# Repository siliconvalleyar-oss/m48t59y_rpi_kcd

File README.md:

# m48t59y_rpi_kcd

Diseño de PCB en KiCad para interfaz M48T59Y (RTC/NVRAM) con PIC18F.

## Estructura

- `m48t59y_pic18f.kicad_pro` - Proyecto principal
- `m48t59y_pic18f.kicad_sch` - Esquemático principal
- `m48t59y_pic18f.kicad_pcb` - Layout PCB

## Módulos

- `power.kicad_sch` - Alimentación
- `mcu.kicad_sch` - Microcontrolador PIC18F
- `m48t59y.kicad_sch` - Circuito M48T59Y
- `txs0108e.kicad_sch` - Traductor de niveles TXS0108E
- `oled.kicad_sch` - Display OLED
- `led_sw.kicad_sch` - LEDs y switches
- `uart.kicad_sch` - UART
- `xt.kicad_sch` - Cristal

## Documentación

Imágenes de referencia en la carpeta `docs/`.

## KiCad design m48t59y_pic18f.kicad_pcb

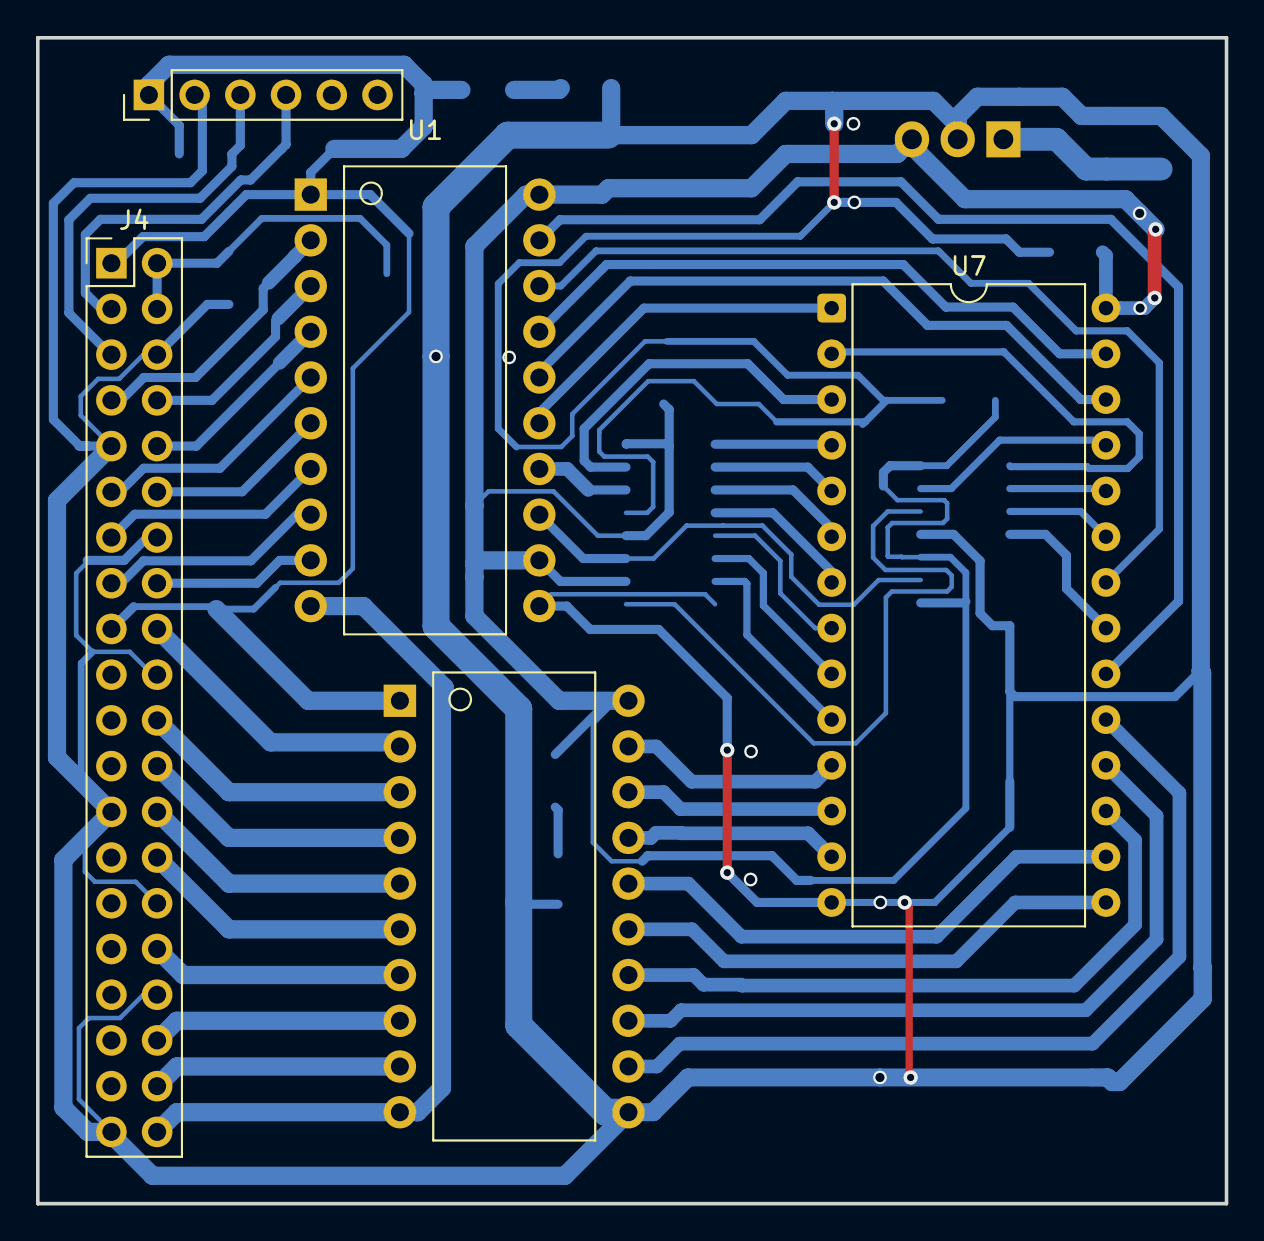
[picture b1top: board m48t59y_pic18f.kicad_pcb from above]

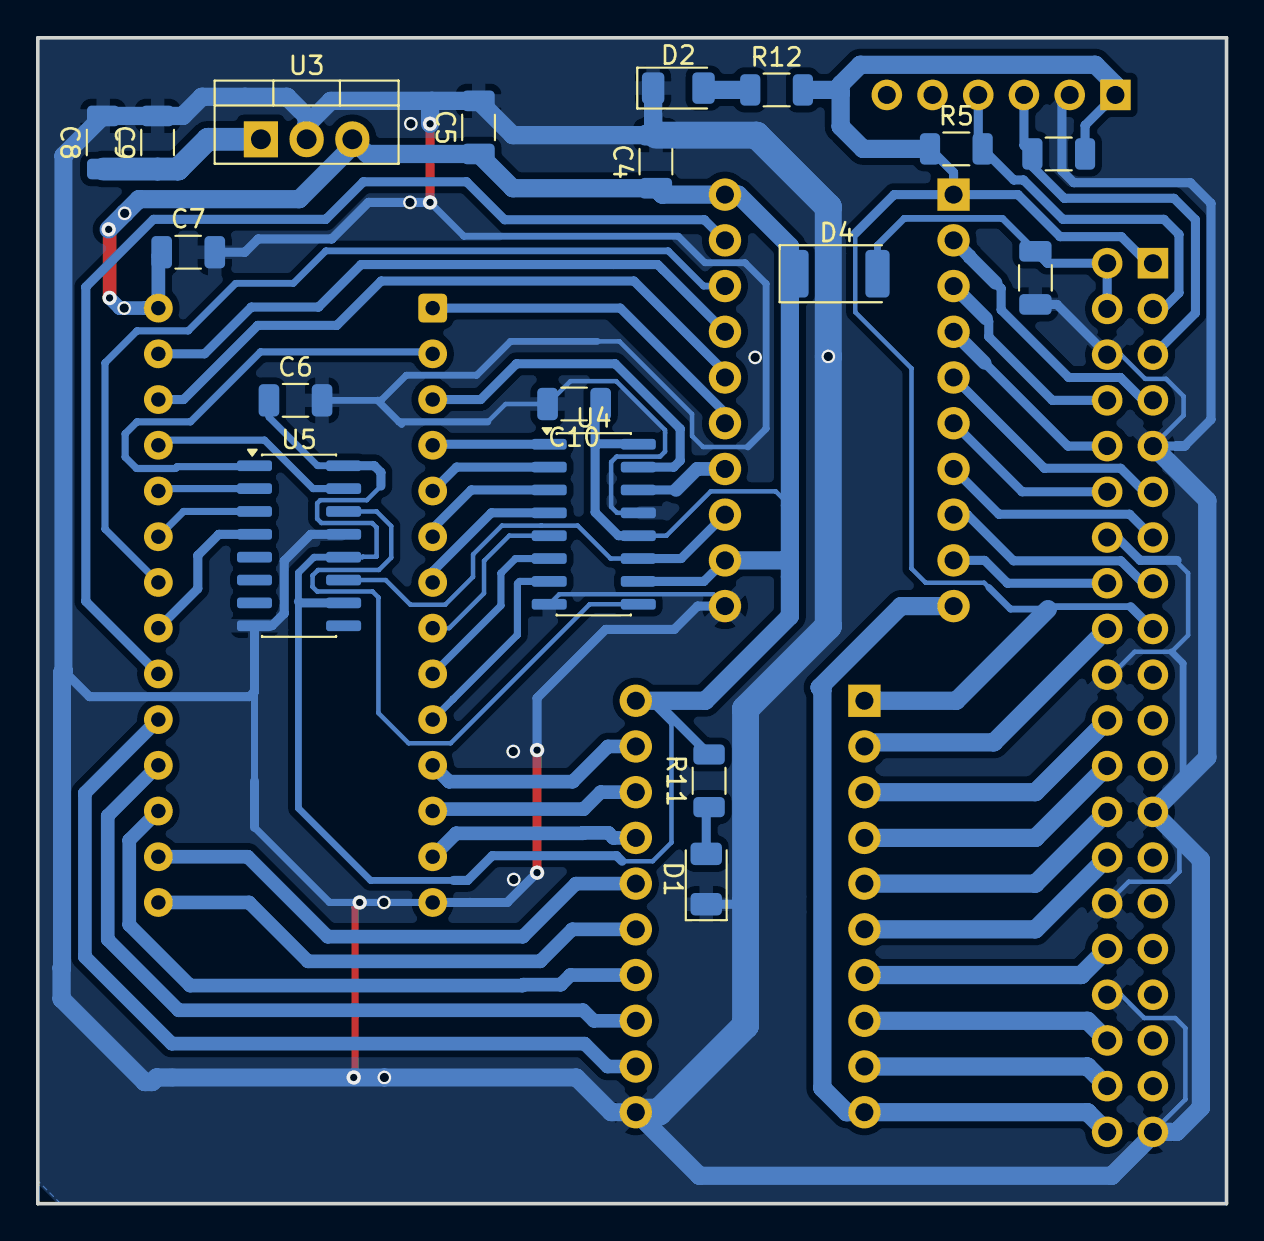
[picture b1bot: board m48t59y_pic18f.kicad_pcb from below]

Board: 2 copper layers, 66.0 x 64.8 mm, 23 parts (18 on the bottom side), 55 nets.

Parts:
C3, C4, C5, C6, C7, C8, C9, C10: 100n; C_1206_3216Metric
D1, D2: LED; LED_1206_3216Metric
D4: 1N4001; D_2010_5025Metric
J3: ssd1306; PinHeader_1x06_P2.54mm_Vertical
J4: Raspberry_Pi_4; PinHeader_2x20_P2.54mm_Vertical
R5, R6, R11, R12: 2k2; R_1206_3216Metric
U1, U2: TXS0108; TXS0108E_THT_20pin
U3: LM7805_TO220; TO-220-3_Vertical
U4, U5: 74HC595; SOIC-16_3.9x9.9mm_P1.27mm
U7: M48T08-150PC; DIP-28_W15.24mm

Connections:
+3V3: J3.1, J4.1 (3V3), J4.17 (3V3), R5.1, R6.1, R12.2, U1.1 (VCCA), U2.1 (VCCA)
+5V: C4.1, C5.1, C6.1, C7.1, C10.1, D4.1 (K), R11.2, U1.12 (B8), U1.20 (VCCB), U2.20 (VCCB), U3.3 (VO), U4.10 (~SRCLR), U4.12 (RCLK), U4.16 (VCC), U5.10 (~SRCLR), U5.12 (RCLK), U5.16 (VCC), U7.28 (VCC)
+12V: C8.1, C9.1, U3.1 (VI)
/RaspberryPi4/GPIO1: J4.28 (ID_SC_I2C0/GPIO01), U2.6 (A5)
/RaspberryPi4/GPIO4: J4.7 (GPCLK0/GPIO04), U1.2 (A1)
/RaspberryPi4/GPIO7: J4.26 (~CE1_SPI0/GPIO07), U2.5 (A4)
/RaspberryPi4/GPIO8: J4.24 (~CE0_SPI0/GPIO08), U2.4 (A3)
/RaspberryPi4/GPIO12: J4.32 (GPIO12/PWM0), U2.7 (A6)
/RaspberryPi4/GPIO14: J4.8 (GPIO14/UART_TXD), U1.3 (A2)
/RaspberryPi4/GPIO15: J4.10 (GPIO15/UART_RXD), U1.4 (A3)
/RaspberryPi4/GPIO16: J4.36 (GPIO16/SPI1_~CE2), U2.8 (A7)
/RaspberryPi4/GPIO17: J4.11 (GPIO17/SPI1_~CE1), U1.5 (A4)
/RaspberryPi4/GPIO18: J4.12 (GPIO18/SPI1_~CE0/PCM_CLK/PWM0), U1.6 (A5)
/RaspberryPi4/GPIO20: J4.38 (GPIO20/SPI1_MOSI/PCM_DIN/PWM1), U2.9 (A8)
/RaspberryPi4/GPIO21: J4.40 (GPIO21/SPI1_SCLK/PCM_DOUT), U1.10 (OE), U2.10 (OE)
/RaspberryPi4/GPIO22: J4.15 (GPIO22/SDIO_CLK), U1.8 (A7)
/RaspberryPi4/GPIO23: J4.16 (GPIO23/SDIO_CMD), U1.9 (A8)
/RaspberryPi4/GPIO24: J4.18 (GPIO24/SDIO_DAT0), U2.2 (A1)
/RaspberryPi4/GPIO25: J4.22 (GPIO25/SDIO_DAT1), U2.3 (A2)
/RaspberryPi4/GPIO27: J4.13 (GPIO27/SDIO_DAT3), U1.7 (A6)
/RaspberryPi4/SCL: J3.3, J4.5 (SCL_I2C1/GPIO03), R6.2
/RaspberryPi4/SDA: J3.4, J4.3 (SDA_I2C1/GPIO02), R5.2
/m48t59y/DQ0: U2.19 (B1), U7.11 (DQ0)
/m48t59y/DQ1: U2.18 (B2), U7.12 (DQ1)
/m48t59y/DQ2: U2.17 (B3), U7.13 (DQ2)
/m48t59y/DQ3: U2.15 (B5), U7.15 (DQ3)
/m48t59y/DQ4: U2.16 (B4), U7.16 (DQ4)
/m48t59y/DQ5: U2.14 (B6), U7.17 (DQ5)
/m48t59y/DQ6: U2.13 (B7), U7.18 (DQ6)
/m48t59y/DQ7: U2.12 (B8), U7.19 (DQ7)
/m48t59y/E1: U1.19 (B1), U7.20 (~E1)
/m48t59y/E2: U1.16 (B4), U7.26 (E2)
/m48t59y/G: U1.18 (B2), U7.22 (~G)
/m48t59y/INT: U1.15 (B5), U7.1 (~INT)
/m48t59y/Q1A: U4.15 (QA), U7.3 (A7)
/m48t59y/Q1B: U4.1 (QB), U7.4 (A6)
/m48t59y/Q1C: U4.2 (QC), U7.5 (A5)
/m48t59y/Q1D: U4.3 (QD), U7.6 (A4)
/m48t59y/Q1E: U4.4 (QE), U7.7 (A3)
/m48t59y/Q1F: U4.5 (QF), U7.8 (A2)
/m48t59y/Q1G: U4.6 (QG), U7.9 (A1)
/m48t59y/Q1H: U4.7 (QH), U7.10 (A0)
/m48t59y/Q2B: U5.1 (QB), U7.2 (A12)
/m48t59y/Q2C: U5.2 (QC), U7.24 (A9)
/m48t59y/Q2D: U5.3 (QD), U7.23 (A11)
/m48t59y/Q2E: U5.4 (QE), U7.21 (A10)
/m48t59y/SER_IN: U1.14 (B6), U4.14 (SER)
/m48t59y/SRCCLK: U1.13 (B7), U4.11 (SRCLK), U5.11 (SRCLK)
/m48t59y/W: U1.17 (B3), U7.27 (~W)
GND: C3.2, C4.2, C5.2, C6.2, C7.2, C8.2, C9.2, C10.2, D1.1 (K), D2.1 (K), J3.2, J4.6 (GND), J4.9 (GND), J4.14 (GND), J4.20 (GND), J4.25 (GND), J4.30 (GND), J4.34 (GND), J4.39 (GND), U1.11 (GND), U2.11 (GND), U3.2 (GND), U4.8 (GND), U4.13 (~OE), U5.8 (GND), U5.13 (~OE), U7.14 (VSS)
unnamed: D1.2 (A), R11.1
unnamed: D2.2 (A), R12.1
unnamed: C3.1, D4.2 (A), J4.2 (5V), J4.4 (5V)
unnamed: U4.9 (QH'), U5.14 (SER)
unnamed: U5.15 (QA), U7.25 (A8)
